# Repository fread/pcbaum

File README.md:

# PCBaum

This was intended to be a "my first soldering" projects for kids, which sadly did not happen. Here are the files anyway, in the hope that they may be of use.

## Choosing the parts

* R1 and R4: 270 Ω give about 20 mA of current assuming a forward voltage of 2 V for each LED.
* R2 and R3: Values may be varied to change the flashing frequency, but the transistor base current must not be exceeded.
* C1 and C2: Values may be varied to change the flashing frequency. Should be rated for at least 9 V. For ease of assembly, prefer non-polar capacitors.
* LEDs: Any will do, but adjust R1/R4 if needed. The board is designed for 3 mm LEDs. For maximum festiveness, angle the LEDs to resemble electric candles sitting on the tree. In this case, 5 mm LEDs can also be used.
* T1 and T2: Virtually anything NPN will do, just mind the pinout.

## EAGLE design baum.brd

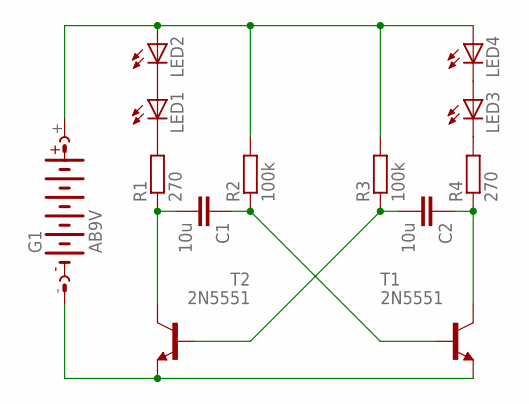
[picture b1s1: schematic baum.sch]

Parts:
C1, C2: 10u; C050-025X075
G1: AB9V
LED1, LED2, LED3, LED4: LED3MM
R1, R4: 270; 0207/10
R2, R3: 100k; 0207/10
T1, T2: 2N5551; TO92-CBE

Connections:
GND: G1.-, T1.E, T2.E
unnamed: C1.2, R1.1, T2.C
unnamed: C2.1, R4.1, T1.C
unnamed: C1.1, R2.1, T1.B
unnamed: C2.2, R3.1, T2.B
unnamed: LED1.K (C), R1.2
unnamed: LED1.A, LED2.K (C)
unnamed: LED3.K (C), R4.2
unnamed: LED3.A, LED4.K (C)
unnamed: G1.+, LED2.A, LED4.A, R2.2, R3.2

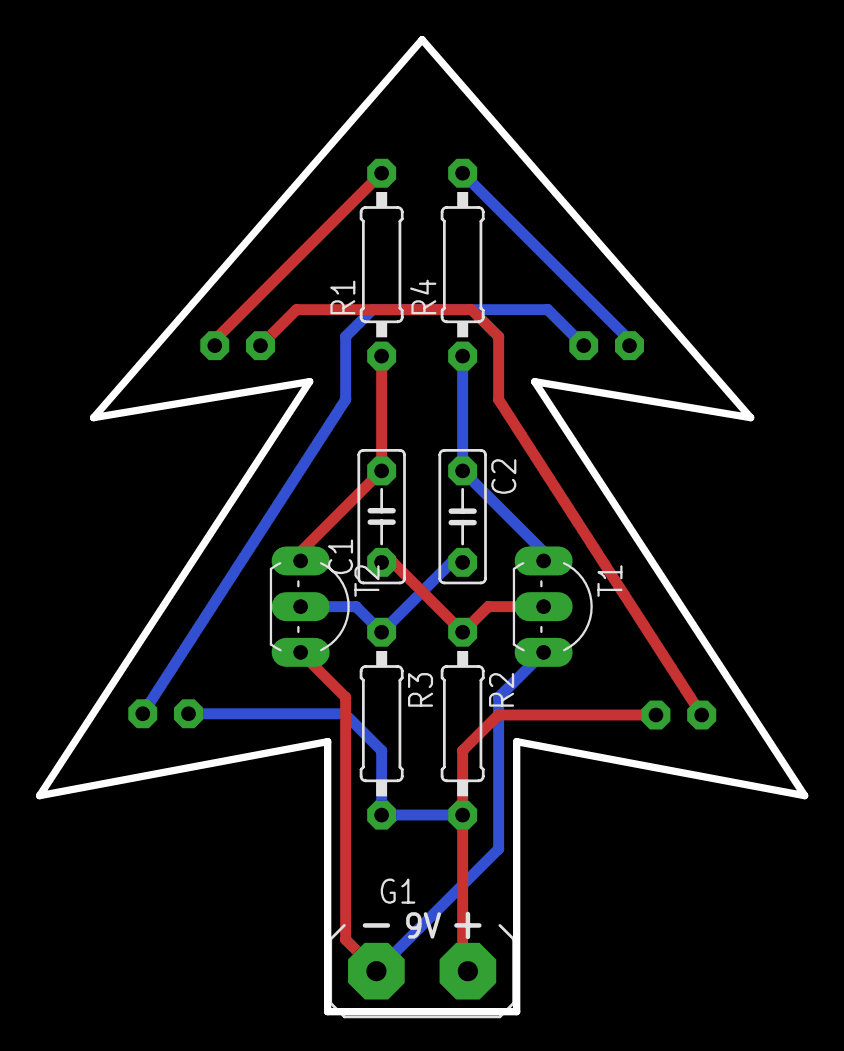
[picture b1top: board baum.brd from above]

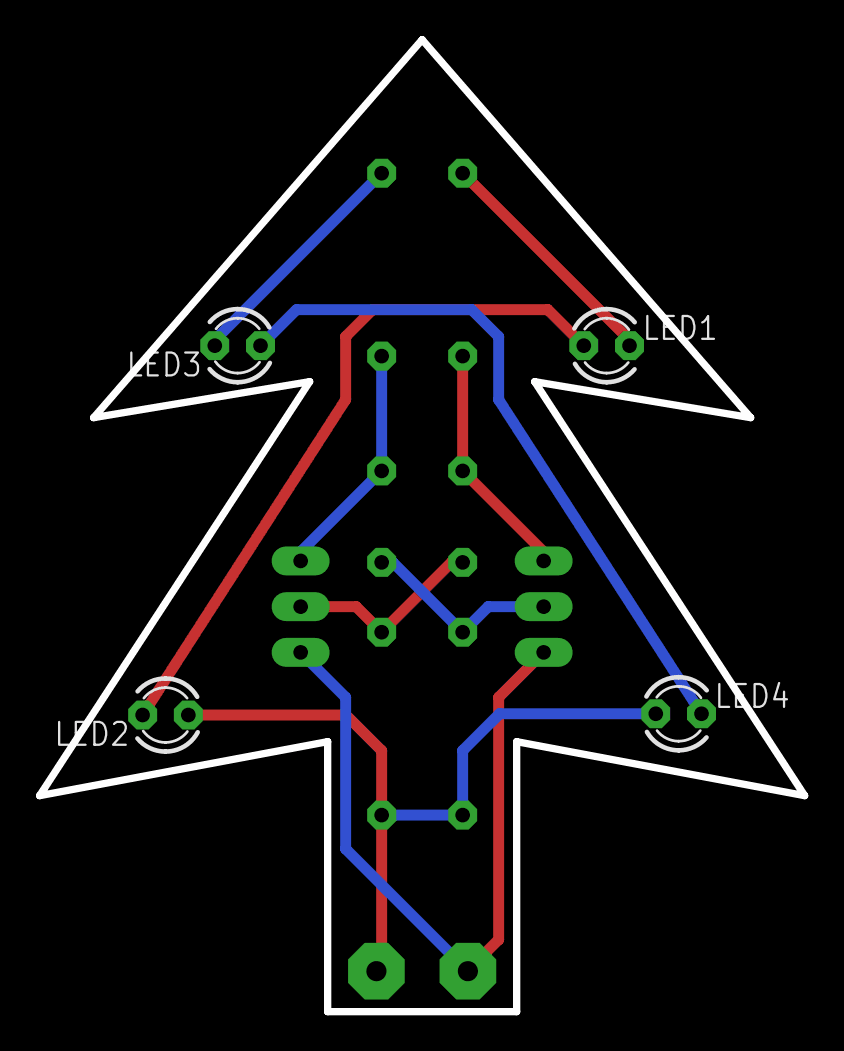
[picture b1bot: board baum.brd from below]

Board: 2 copper layers, 42.5 x 54.0 mm, 13 parts (4 on the bottom side), 10 nets.

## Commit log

2014-11-27 Initial commit.
2015-01-11 Move README to README.md.
